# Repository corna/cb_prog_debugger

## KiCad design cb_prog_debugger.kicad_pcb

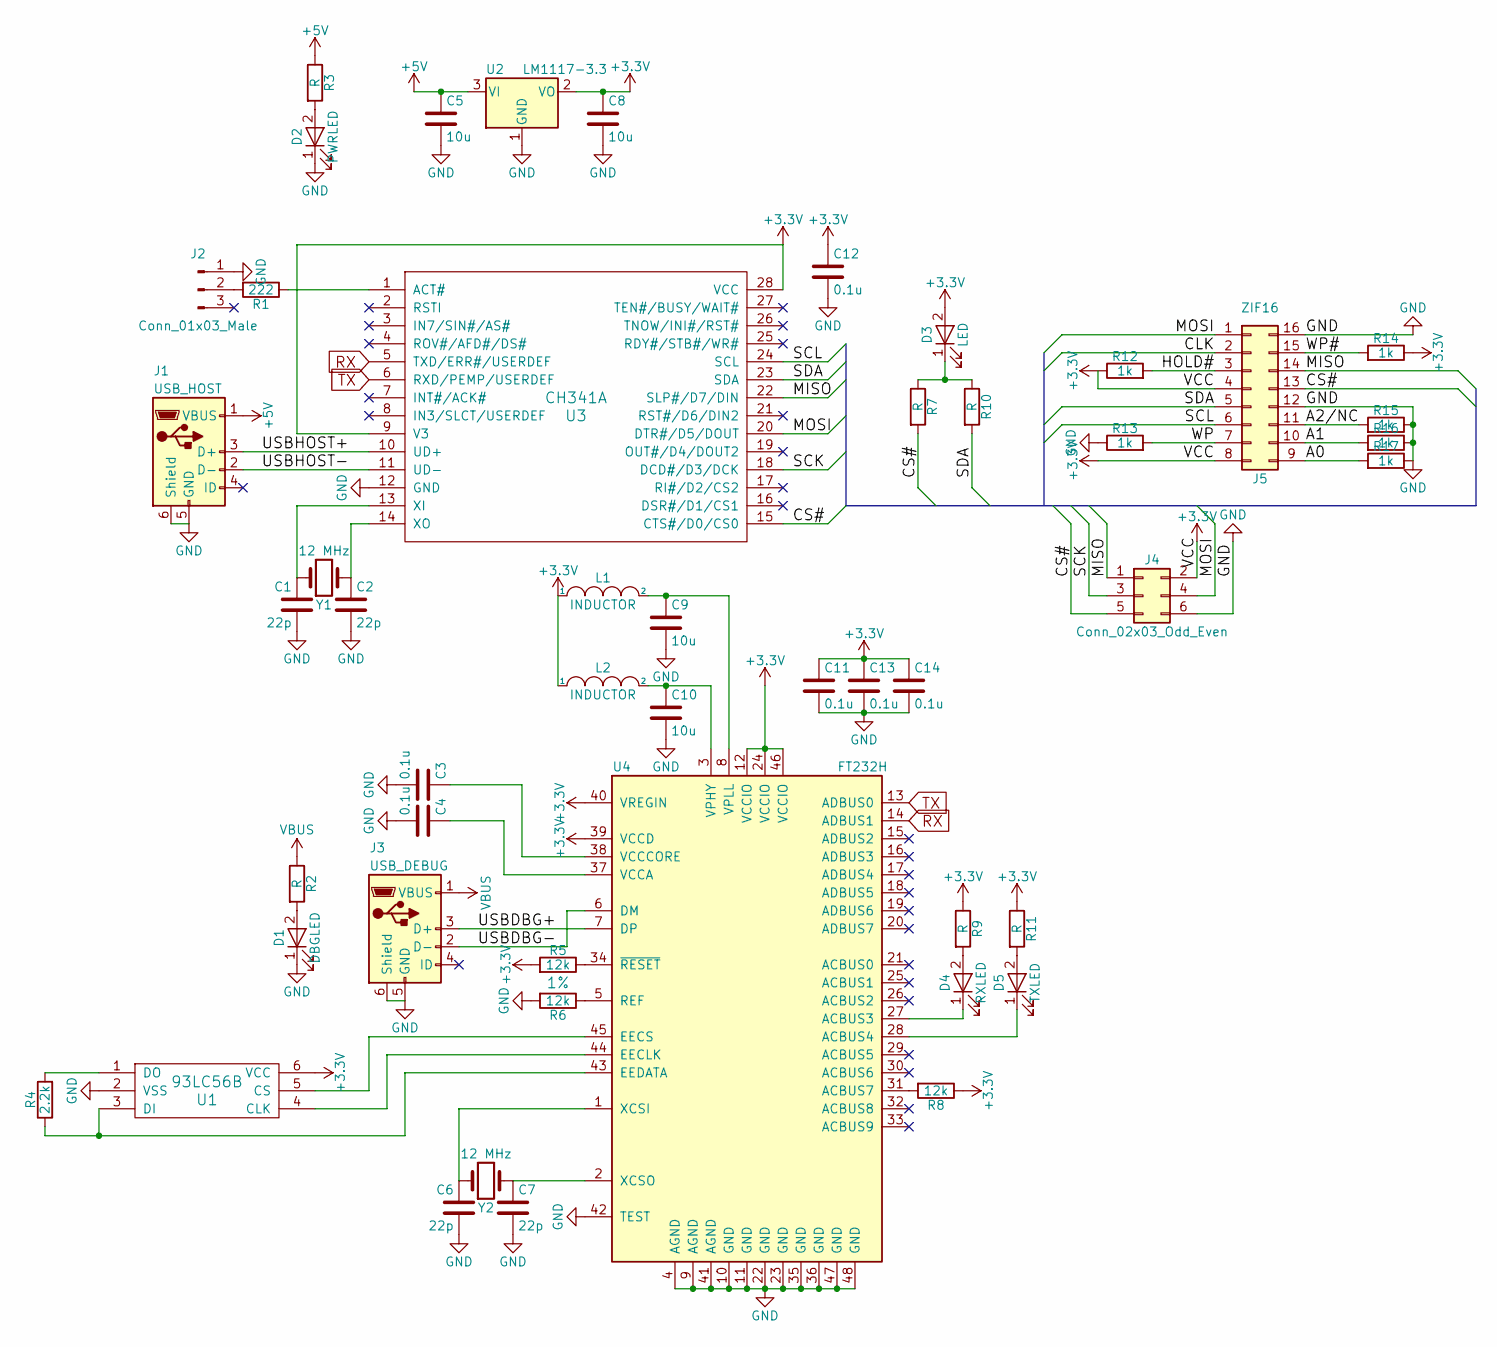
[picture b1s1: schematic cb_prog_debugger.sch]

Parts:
C1, C2, C6, C7: 22p; C_0805
C3, C4, C11, C12, C13, C14: 0.1u; C_0805
C5, C8, C9, C10: 10u; C_0805
D1: DBGLED; LED_0805
D2: PWRLED; LED_0805
D3: LED; LED_0805
D4: RXLED; LED_0805
D5: TXLED; LED_0805
J1: USB_HOST; USB_Micro-B
J2: Conn_01x03_Male; Pin_Header_Straight_1x03_Pitch2.54mm
J3: USB_DEBUG; USB_Micro-B
J4: Conn_02x03_Odd_Even; Pin_Header_Straight_2x03_Pitch2.54mm
J5: ZIF16
L1, L2: INDUCTOR; L_0805
R1: 222; R_0805
R2, R3, R7, R9, R10, R11: R; R_0805
R4: 2.2k; R_0805
R5, R6, R8: 12k; R_0805
R12, R13, R14, R15, R16, R17: 1k; R_0805
U1: 93LC56B; SOT-23-6
U2: LM1117-3.3; SOT-223-3Lead_TabPin2
U3: CH341A; SOIC-28
U4: FT232H; LQFP-48_7x7mm_Pitch0.5mm
Y1, Y2: 12 MHz; Crystal_SMD_5032-2pin_5.0x3.2mm

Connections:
+3V3: C8.1, C11.1, C12.1, C13.1, C14.1, D3.2 (A), J4.2, J5.4, J5.8, L1.1, L2.1, R5.2, R8.1, R9.1, R11.1, R12.1, R14.1, U1.6 (VCC), U2.2 (VO), U3.9 (V3), U3.28 (VCC), U4.12 (VCCIO), U4.24 (VCCIO), U4.39 (VCCD), U4.40 (VREGIN), U4.46 (VCCIO)
+5V: C5.1, J1.1 (VBUS), R3.1, U2.3 (VI)
/A0: J5.9, R17.2
/A1: J5.10, R16.2
/A2/NC: J5.11, R15.2
/CLK: J5.2
/CS#: J4.5, J5.13, R7.2, U3.15 (CTS#/D0/CS0)
/HOLD#: J5.3, R12.2
/MISO: J4.1, J5.14, U3.22 (SLP#/D7/DIN)
/MOSI: J4.4, J5.1, U3.20 (DTR#/D5/DOUT)
/SCK: J4.3, U3.18 (DCD#/D3/DCK)
/SCL: J5.6, U3.24 (SCL)
/SDA: J5.5, R10.2, U3.23 (SDA)
/USBDBG+: J3.3 (D+), U4.7 (DP)
/USBDBG-: J3.2 (D-), U4.6 (DM)
/USBHOST+: J1.3 (D+), U3.10 (UD+)
/USBHOST-: J1.2 (D-), U3.11 (UD-)
/WP: J5.7, R13.2
/WP#: J5.15, R14.2
GND: C1.2, C2.2, C3.2, C4.2, C5.2, C6.2, C7.2, C8.2, C9.2, C10.2, C11.2, C12.2, C13.2, C14.2, D1.1 (K), D2.1 (K), J1.5 (GND), J1.6 (Shield), J2.1, J3.5 (GND), J3.6 (Shield), J4.6, J5.12, J5.16, R6.2, R13.1, R15.1, R16.1, R17.1, U1.2 (VSS), U2.1 (GND), U3.12 (GND), U4.4 (AGND), U4.9 (AGND), U4.10 (GND), U4.11 (GND), U4.22 (GND), U4.23 (GND), U4.35 (GND), U4.36 (GND), U4.41 (AGND), U4.42 (TEST), U4.47 (GND), U4.48 (GND)
unnamed: C1.1, U3.13 (XI), Y1.1
unnamed: C2.1, U3.14 (XO), Y1.2
unnamed: C3.1, U4.38 (VCCCORE)
unnamed: C4.1, U4.37 (VCCA)
unnamed: C6.1, U4.1 (XCSI), Y2.1
unnamed: C7.1, U4.2 (XCSO), Y2.2
unnamed: C9.1, L1.2, U4.8 (VPLL)
unnamed: C10.1, L2.2, U4.3 (VPHY)
unnamed: D1.2 (A), R2.2
unnamed: D2.2 (A), R3.2
unnamed: D3.1 (K), R7.1, R10.1
unnamed: D4.1 (K), U4.27 (ACBUS3)
unnamed: D4.2 (A), R9.2
unnamed: D5.1 (K), U4.28 (ACBUS4)
unnamed: D5.2 (A), R11.2
unnamed: J2.2, R1.2
unnamed: R1.1, U3.1 (ACT#)
unnamed: R4.1, U1.3 (DI), U4.43 (EEDATA)
unnamed: R4.2, U1.1 (DO)
unnamed: R5.1, U4.34 (~RESET)
unnamed: R6.1, U4.5 (REF)
unnamed: R8.2, U4.31 (ACBUS7)
unnamed: U1.4 (CLK), U4.44 (EECLK)
unnamed: U1.5 (CS), U4.45 (EECS)
RX: U3.5 (TXD/ERR#/USERDEF), U4.14 (ADBUS1)
TX: U3.6 (RXD/PEMP/USERDEF), U4.13 (ADBUS0)
VBUS: J3.1 (VBUS), R2.1

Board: 2 copper layers, 49 parts (30 on the bottom side), 46 nets, no tracks yet.

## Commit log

2018-01-08 Remove obsolete ch34x.lib
2018-01-08 Set correct design rules
2018-01-08 Add differential net names
2018-01-08 Fix shorted 3.3V-GND
2018-01-08 Use 0805 packages
2018-01-12 PCB: Add initial component layout
